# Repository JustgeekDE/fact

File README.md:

# Simple Fact
## Overview
Simple Fact (a simple **F**lash **a**nd **c**amera **t**rigger) is a smallish ([SoB 5x5](http://dangerousprototypes.com/docs/Sick_of_Beige_standard_PCB_sizes_v1.0)) tool to automatically trigger a a camera or camera flash based on sounds or light impulses.

The whole system is planned to be Arduino compatible to allow easy extension.

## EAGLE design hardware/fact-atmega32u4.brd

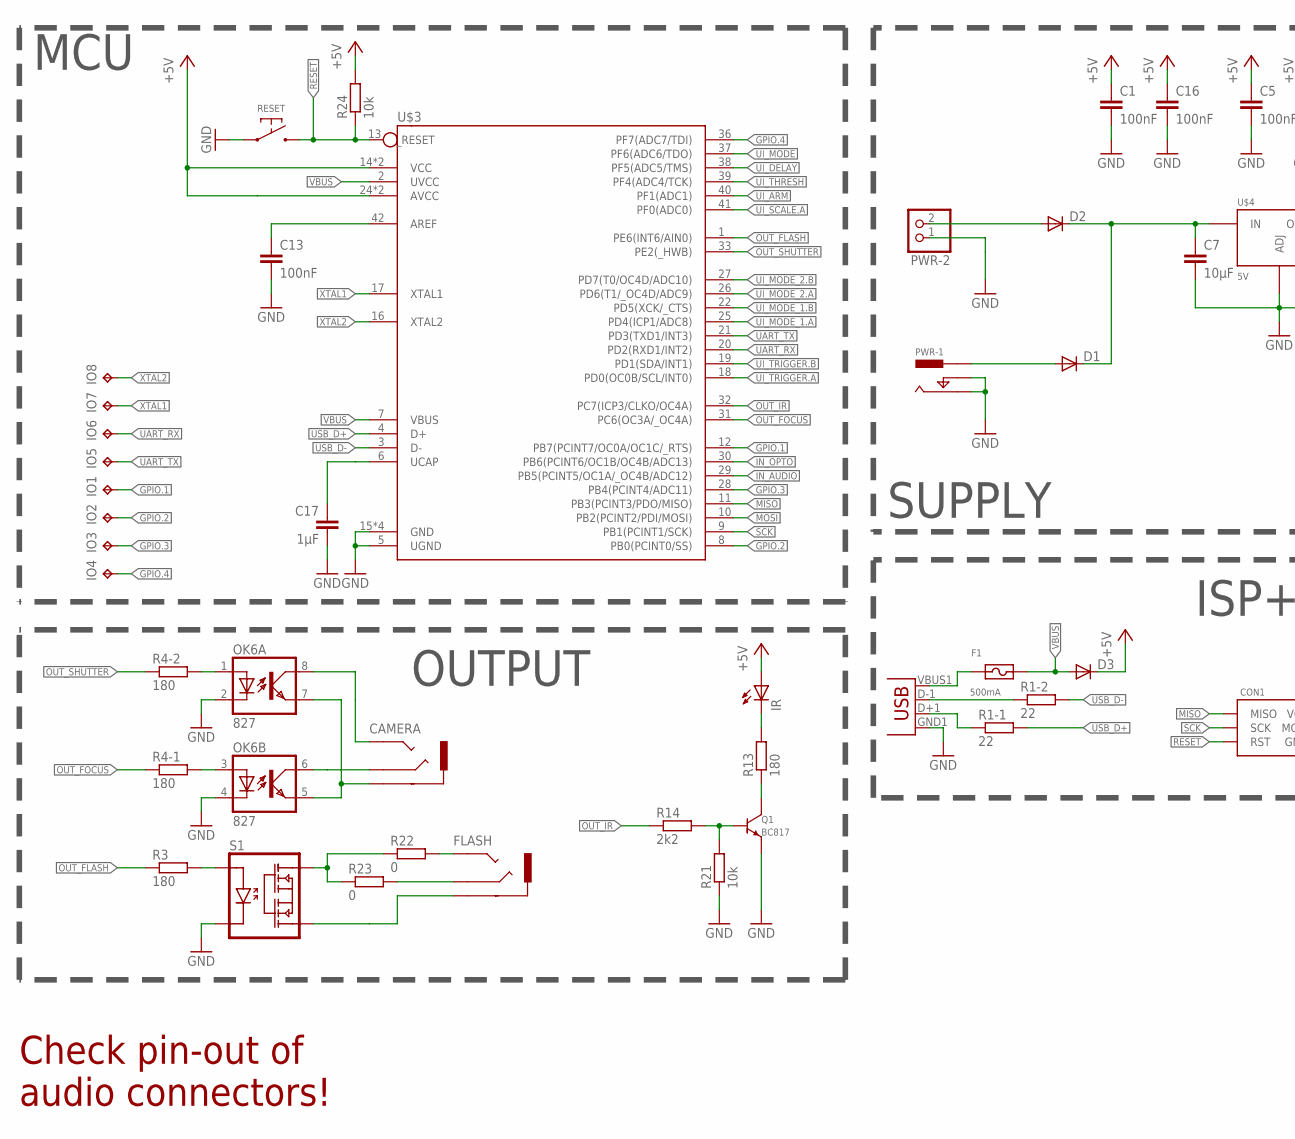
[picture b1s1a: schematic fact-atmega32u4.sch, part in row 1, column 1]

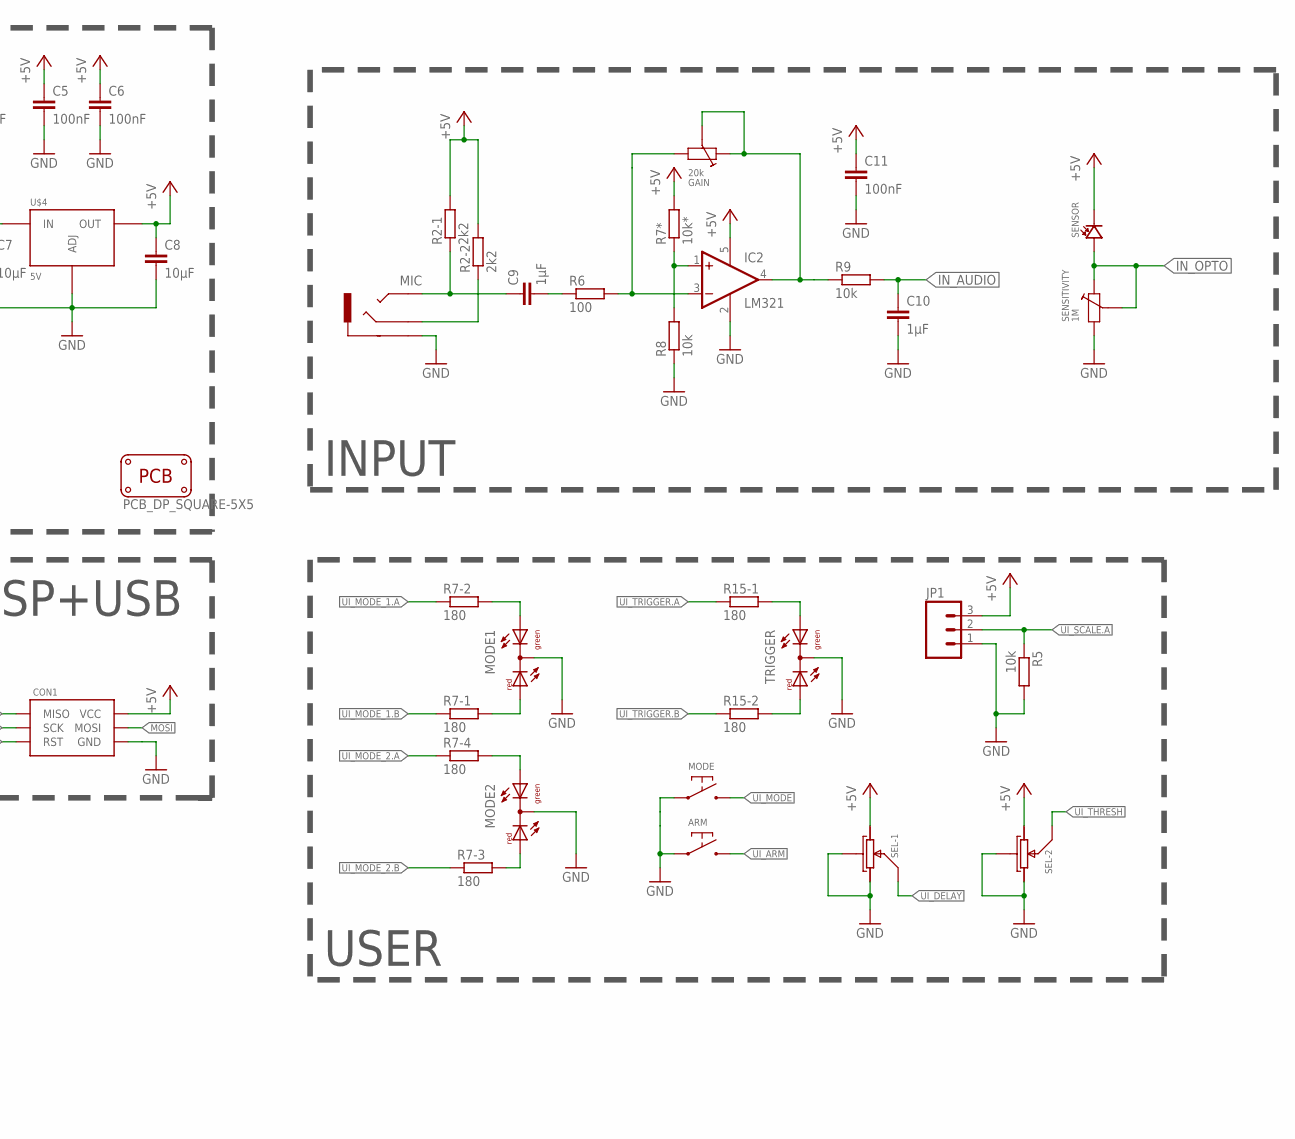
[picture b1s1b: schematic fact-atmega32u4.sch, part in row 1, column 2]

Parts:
ARM: SWITCH-DEFAULT_OFF-DEFAULT; SWITCH-GENERIC-4_PIN
C1, C5, C6, C11, C13, C16: 100nF; C0603
C7, C8: 10µF; C0603
C9, C10, C17: 1µF; C0603
CAMERA: AUDIO-STEREO2MM5; AUDIO-STEREO-2MM5-SJ1-2503A
CON1: ISP-6_PIN-POGO; POGO-1.27-6_PIN-MADWORM
D1, D2, D3: DIODESOD; SOD-323
F1: 500mA; SMD-0805
FLASH: AUDIO-STEREODEALEXTREME; AUDIO-STEREO-3MM5-ST-009
GAIN: 20k; TRIM-POT-CA6-VS5
IC2: LM321; SOT23-5
IO1, IO2, IO3, IO4, IO5, IO6, IO7, IO8: TPTP15R; TP15R
IR: LED5MM
JP1: M03LOCK; 1X03_LOCK
MIC: AUDIO-STEREODEALEXTREME; AUDIO-STEREO-3MM5-ST-009
MODE: SWITCH-DEFAULT_OFF-DEFAULT; SWITCH-GENERIC-4_PIN
MODE1, MODE2: DUOLED-RG-C; DUOLED-C-5MM
OK6: 827; SMD08
PCB1: PCB_DP_SQUARE-5X5; DP5050_V1
PWR-1: POWER-BARREL_JACKEBAY; POWER-BARREL-2MM1-EBAY
PWR-2: PINHD-1X2; 1X02
Q1: BC817; SOT23
R1: 22; R-ARRAY-2X-0603
R2: 2k2; R-ARRAY-2X-0603
R3, R13: 180; R0603
R4, R15: 180; R-ARRAY-2X-0603
R5, R8, R9, R21, R24: 10k; R0603
R6: 100; R0603
R7: 180; R-ARRAY-4X-CTS-0603
R7*: 10k*; R0603
R14: 2k2; R0603
R22, R23: 0; R1206
RESET: SWITCH-DEFAULT_OFF-SMD-2_PIN; SWITCH-SMD-2_PIN-DX
S1: RELAYLH1500; SMD-06
SEL: DUAL-POT; POT-DUAL-P090
SENSITIVITY: 1M; TRIM-POT-CA6-VS5
SENSOR: PHOTODIODE; LED-5MM
TRIGGER: DUOLED-RG-C; DUOLED-C-5MM
U$3: ATMEGA32U4-QFN-HAND; QFN-44-NOPAD-LONGLEADS
U$4: 5V; SOT223
U$5: USB; USB-AB-MICRO-SMD_V03

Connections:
+5V: C1.1, C5.1, C6.1, C8.1, C11.1, C16.1, CON1.P$2 (VCC), D3.1 (C), IC2.5 (V+), IR.A, JP1.3, R2.P$1.2 (2), R2.P$2.2 (2), R7*.2, R24.2, SEL.P1-3 (B), SEL.P2-1 (A), SENSOR.K (C), U$3.14 (VCC), U$3.24 (AVCC), U$3.34 (VCC), U$3.44 (AVCC), U$4.2 (OUT), U$4.4 (OUT)
GND: ARM.P$1, ARM.P$2, C1.2, C5.2, C6.2, C7.2, C8.2, C10.2, C11.2, C13.2, C16.2, C17.2, CON1.P$6 (GND), IC2.2 (V-), JP1.1, MIC.P$1.1 (SLEEVE), MIC.P$1.2 (SLEEVE), MODE.P$1, MODE.P$2, MODE1.C, MODE2.C, OK6.2 (C), OK6.4 (C), PWR-1.P$2 (SWITCH), PWR-1.P$3 (OUTER), PWR-2.1, Q1.P$2 (EMITTER), R5.2, R8.1, R21.1, RESET.P$1, S1.2 (LED-C), SEL.CENTER (SHIELD), SEL.G1-S (SHIELD), SEL.G2-S (SHIELD), SEL.P1-1 (A), SEL.P2-3 (B), SENSITIVITY.P$2, TRIGGER.C, U$3.5 (UGND), U$3.15 (GND), U$3.23 (GND), U$3.35 (GND), U$3.43 (GND), U$4.1 (ADJ), U$5.GND1 (GND)
GPIO.1: IO1.TP, U$3.12 (PB7(PCINT7/OC0A/OC1C/_RTS))
GPIO.2: IO2.TP, U$3.8 (PB0(PCINT0/SS))
GPIO.3: IO3.TP, U$3.28 (PB4(PCINT4/ADC11))
GPIO.4: IO4.TP, U$3.36 (PF7(ADC7/TDI))
HV_OUT: R22.1, R23.1, S1.6 (R1)
HV_RING: FLASH.P$2 (RING), R23.2
HV_SLEEVE: FLASH.P$1.1 (SLEEVE), FLASH.P$1.2 (SLEEVE), S1.4 (R2)
HV_TIP: FLASH.P$3.1 (TIP), FLASH.P$3.2 (TIP), R22.2
IN_AUDIO: C10.1, R9.2, U$3.29 (PB5(PCINT5/OC1A/_OC4B/ADC12))
IN_OPTO: SENSITIVITY.CENTER, SENSITIVITY.P$1, SENSOR.A, U$3.30 (PB6(PCINT6/OC1B/OC4B/ADC13))
MISO: CON1.P$1 (MISO), U$3.11 (PB3(PCINT3/PDO/MISO))
MOSI: CON1.P$4 (MOSI), U$3.10 (PB2(PCINT2/PDI/MOSI))
unnamed: C7.1, D1.1 (C), D2.1 (C), U$4.3 (IN)
unnamed: F1.1, U$5.VBUS1 (VBUS)
unnamed: R1.P$2.1 (1), U$5.D-1 (D-)
unnamed: D1.2 (A), PWR-1.P$4 (CENTER)
unnamed: R1.P$1.1 (1), U$5.D+1 (D+)
unnamed: D2.2 (A), PWR-2.2
unnamed: CAMERA.P$1 (SLEEVE), OK6.5 (EMIT), OK6.7 (EMIT)
unnamed: CAMERA.P$4 (RING), OK6.6 (COL)
unnamed: CAMERA.P$2 (TIP), CAMERA.P$3 (TIP), OK6.8 (COL)
unnamed: OK6.1 (A), R4.P$2.2 (2)
unnamed: MIC.P$2 (RING), R2.P$2.1 (1)
unnamed: C9.1, MIC.P$3.1 (TIP), MIC.P$3.2 (TIP), R2.P$1.1 (1)
unnamed: IC2.1 (+IN), R7*.1, R8.2
unnamed: C9.2, R6.1
unnamed: GAIN.P$2, IC2.3 (-IN), R6.2
unnamed: GAIN.CENTER, GAIN.P$1, IC2.4 (OUT), R9.1
unnamed: R3.2, S1.1 (LED-A)
unnamed: OK6.3 (A), R4.P$1.2 (2)
unnamed: Q1.P$3 (COLLECTOR), R13.1
unnamed: IR.K (C), R13.2
unnamed: Q1.P$1 (BASE), R14.2, R21.2
unnamed: MODE1.AX (AG), R7.P$2.2 (2)
unnamed: MODE1.AR, R7.P$1.2 (2)
unnamed: R15.P$1.2 (2), TRIGGER.AX (AG)
unnamed: R15.P$2.2 (2), TRIGGER.AR
unnamed: MODE2.AX (AG), R7.P$4.2 (2)
unnamed: MODE2.AR, R7.P$3.2 (2)
unnamed: C13.1, U$3.42 (AREF)
unnamed: C17.1, U$3.6 (UCAP)
OUT_FLASH: R3.1, U$3.1 (PE6(INT6/AIN0))
OUT_FOCUS: R4.P$1.1 (1), U$3.31 (PC6(OC3A/_OC4A))
OUT_IR: R14.1, U$3.32 (PC7(ICP3/CLKO/OC4A))
OUT_SHUTTER: R4.P$2.1 (1), U$3.33 (PE2(_HWB))
RESET: CON1.P$5 (RST), R24.1, RESET.P$2, U$3.13 (_RESET)
SCK: CON1.P$3 (SCK), U$3.9 (PB1(PCINT1/SCK))
UART_RX: IO6.TP, U$3.20 (PD2(RXD1/INT2))
UART_TX: IO5.TP, U$3.21 (PD3(TXD1/INT3))
UI_ARM: ARM.P$3, ARM.P$4, U$3.40 (PF1(ADC1))
UI_DELAY: SEL.P1-2 (M), U$3.38 (PF5(ADC5/TMS))
UI_MODE: MODE.P$3, MODE.P$4, U$3.37 (PF6(ADC6/TDO))
UI_MODE_1.A: R7.P$2.1 (1), U$3.25 (PD4(ICP1/ADC8))
UI_MODE_1.B: R7.P$1.1 (1), U$3.22 (PD5(XCK/_CTS))
UI_MODE_2.A: R7.P$4.1 (1), U$3.26 (PD6(T1/_OC4D/ADC9))
UI_MODE_2.B: R7.P$3.1 (1), U$3.27 (PD7(T0/OC4D/ADC10))
UI_SCALE.A: JP1.2, R5.1, U$3.41 (PF0(ADC0))
UI_THRESH: SEL.P2-2 (M), U$3.39 (PF4(ADC4/TCK))
UI_TRIGGER.A: R15.P$1.1 (1), U$3.18 (PD0(OC0B/SCL/INT0))
UI_TRIGGER.B: R15.P$2.1 (1), U$3.19 (PD1(SDA/INT1))
USB_D+: R1.P$1.2 (2), U$3.4 (D+)
USB_D-: R1.P$2.2 (2), U$3.3 (D-)
VBUS: D3.2 (A), F1.2, U$3.2 (UVCC), U$3.7 (VBUS)
XTAL1: IO7.TP, U$3.17 (XTAL1)
XTAL2: IO8.TP, U$3.16 (XTAL2)

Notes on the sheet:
INPUT
OUTPUT
USER
SUPPLY
MCU
Check pin-out of audio connectors!
ISP+USB

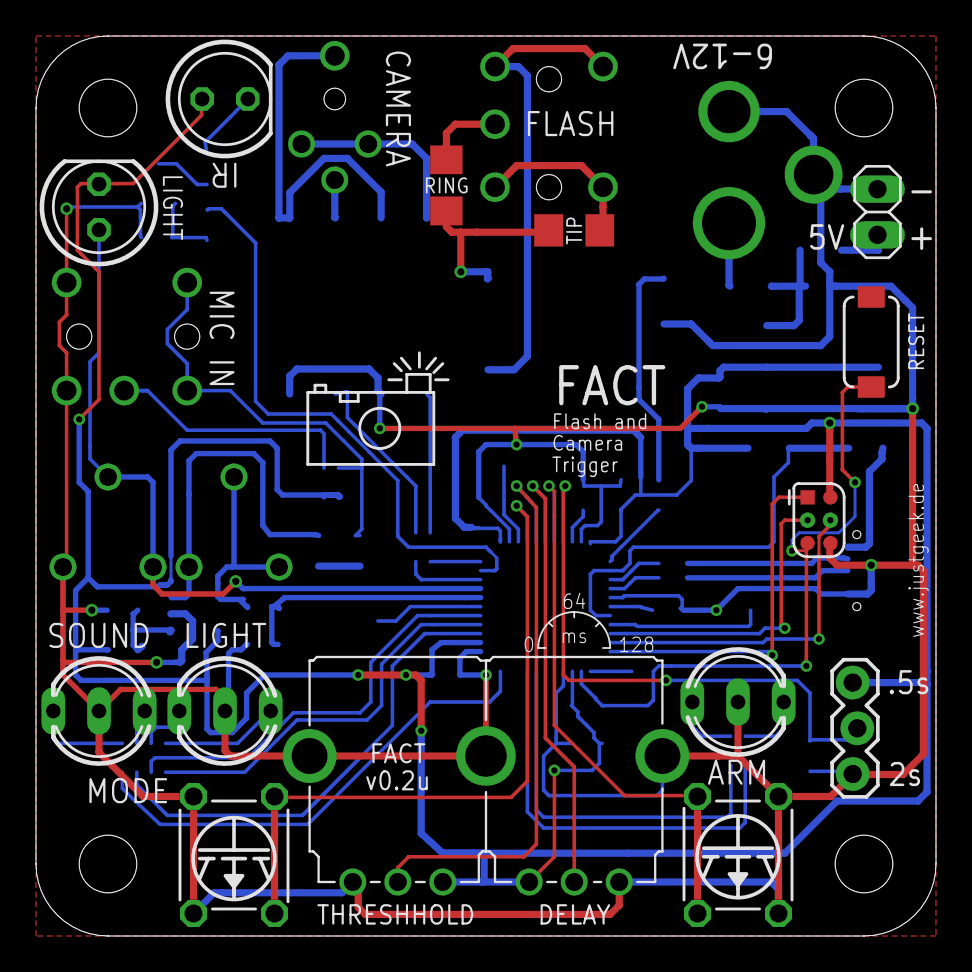
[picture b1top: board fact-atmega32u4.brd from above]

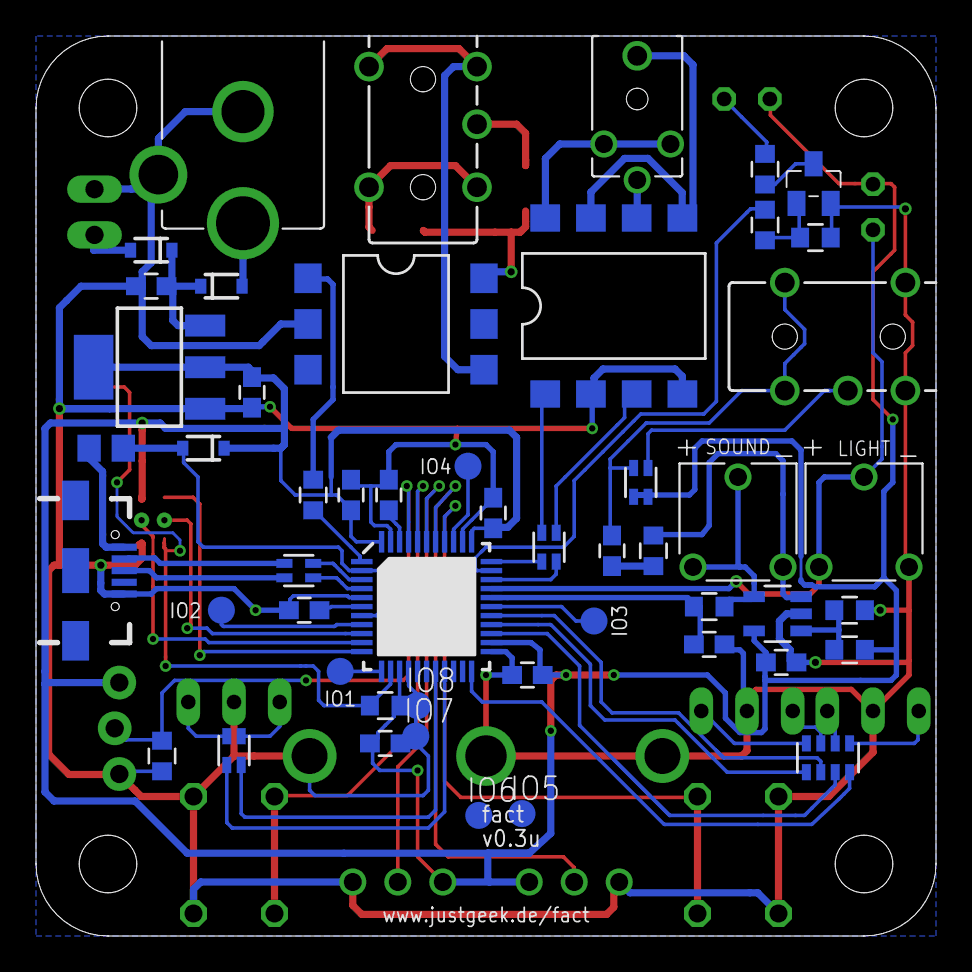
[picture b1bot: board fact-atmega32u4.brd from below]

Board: 2 copper layers, 50.0 x 50.0 mm, 70 parts (52 on the bottom side), 67 nets.

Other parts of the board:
U$1, U$2: LOGO-JUSTGEEK-XS
U$6, U$7: LOGO-JUSTGEEK-XXXS-MASK

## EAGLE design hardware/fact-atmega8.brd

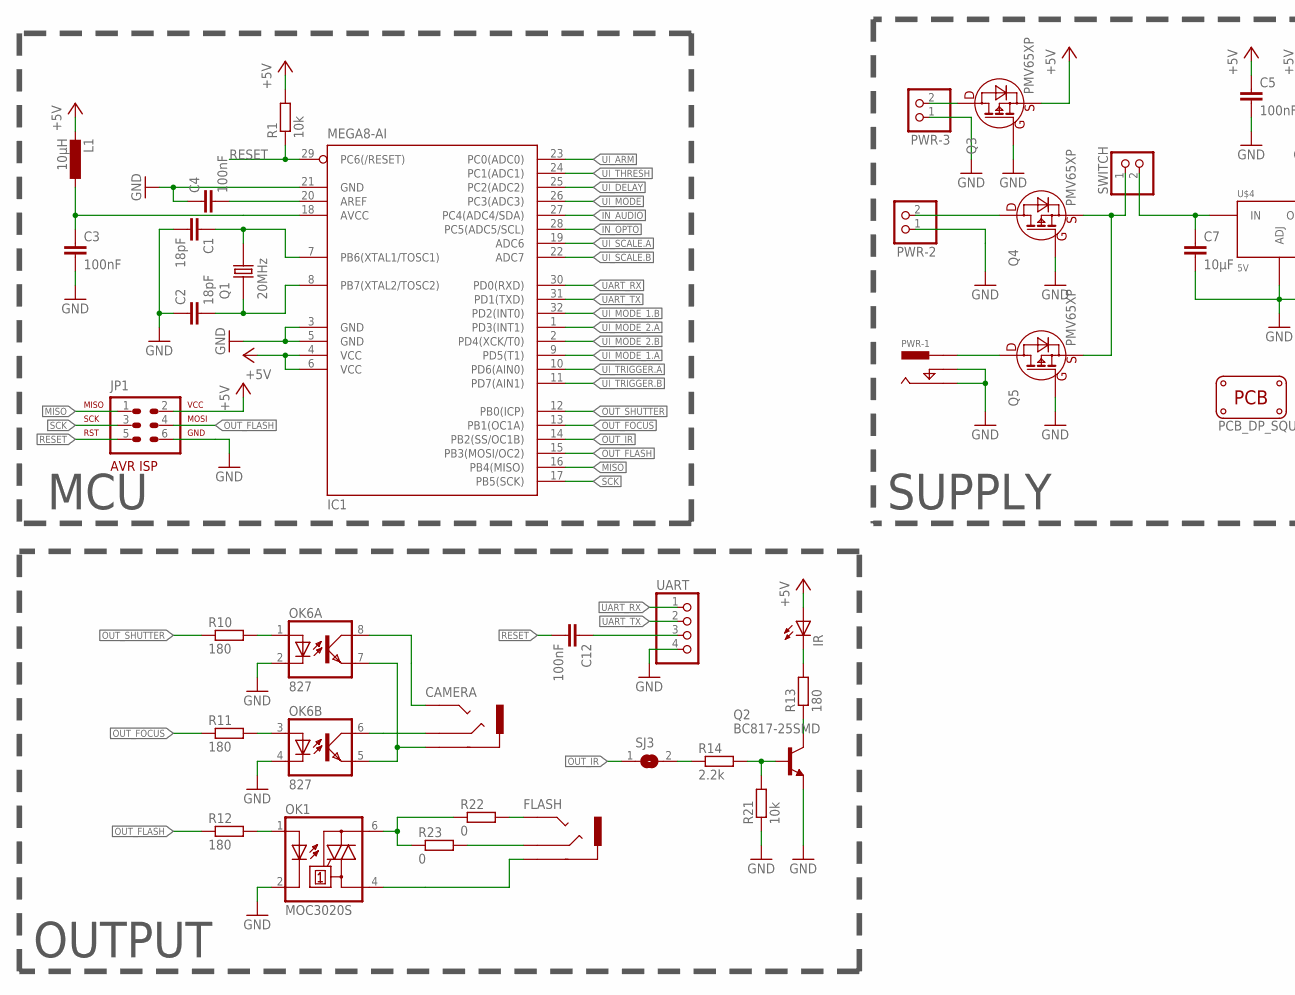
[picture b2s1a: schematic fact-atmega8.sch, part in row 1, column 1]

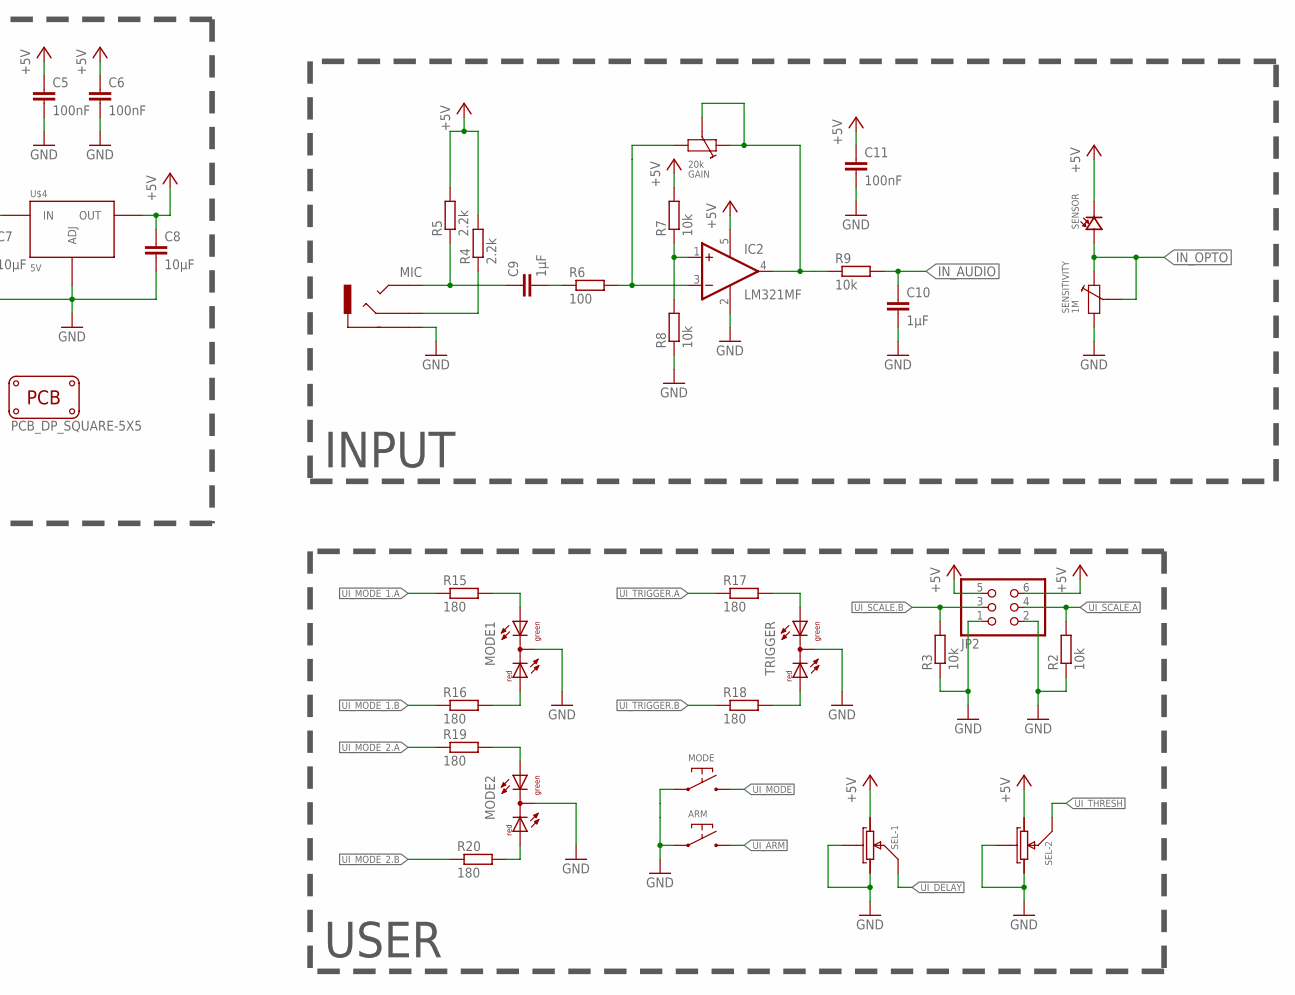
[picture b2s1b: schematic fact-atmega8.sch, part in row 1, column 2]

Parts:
ARM: SWITCH-DEFAULT_OFF; SWITCH-GENERIC-4_PIN
C1, C2: 18pF; C0603
C3, C4, C5, C6, C11, C12: 100nF; C0603
C7, C8: 10µF; C0603
C9, C10: 1µF; C0603
CAMERA: AUDIO-STEREO2MM5; AUDIO-STEREO-2MM5-SJ1-2503A
FLASH: AUDIO-STEREOCONRAD; AUDIO-STEREO-CONRAD-KB3-3_PIN
GAIN: 20k; TRIM-POT-CA6-VS5
IC1: MEGA8-AI; TQFP32-08
IC2: LM321MF; SOT23-5
IR: LED5MM
JP1: AVR-ISP-6VERT; AVR-ISP-6
JP2: PINHD-2X3; 2X03
L1: 10µH; R0805
MIC: AUDIO-STEREOCONRAD-KB3; AUDIO-STEREO-CONRAD-KB3-3_PIN
MODE: SWITCH-DEFAULT_OFF; SWITCH-GENERIC-4_PIN
MODE1, MODE2: DUOLED-RG-C; DUOLED-C-5MM
OK1: MOC3020S; DIL6-SMD
OK6: 827; SMD08
PCB1: PCB_DP_SQUARE-5X5; DP5050_V1
PWR-1: POWER-BARREL_JACKPJ-102A; POWER-BARREL-2MM1-PJ_102A
PWR-2, PWR-3: PINHD-1X2; 1X02
Q1: 20MHz; CRYSTAL-SMD-5MM_X_3.2MM
Q2: BC817-25SMD; SOT23-BEC
Q3, Q4, Q5: PMV65XP; SOT23
R1, R2, R3, R7, R8, R9, R21: 10k; R0603
R4, R5, R14: 2.2k; R0603
R6: 100; R0603
R10, R11, R12, R13, R15, R16, R17, R18, R19, R20: 180; R0603
R22, R23: 0; R1206
SEL: DUAL-POT; POT-DUAL-P090
SENSITIVITY: 1M; TRIM-POT-CA6-VS5
SENSOR: PHOTODIODE; LED-5MM
SJ3: SJ
SWITCH: PINHD-1X2; 1X02
TRIGGER: DUOLED-RG-C; DUOLED-C-5MM
U$4: 5V; SOT223
UART: PINHD-1X4; 1X04

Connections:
+5V: C5.1, C6.1, C8.1, C11.1, IC1.4 (VCC), IC1.6 (VCC), IC2.5 (V+), IR.A, JP1.2, JP2.5, JP2.6, L1.2, Q3.P$2 (SOURCE), R1.2, R4.2, R5.2, R7.2, SEL.P1-3 (B), SEL.P2-1 (A), SENSOR.K (C), U$4.2 (OUT)
GND: ARM.P$1, ARM.P$2, C1.2, C2.1, C3.2, C4.1, C5.2, C6.2, C7.2, C8.2, C10.2, C11.2, IC1.3 (GND), IC1.5 (GND), IC1.21 (GND), IC2.2 (V-), JP1.6, JP2.1, JP2.2, MIC.2.1 (SLEEVE), MIC.2.2 (SLEEVE), MODE.P$1, MODE.P$2, MODE1.C, MODE2.C, OK1.2 (C), OK6.2 (C), OK6.4 (C), PWR-1.P$2 (OUTER), PWR-1.P$3 (SWITCH), PWR-2.1, PWR-3.1, Q2.E, Q3.P$1 (GATE), Q4.P$1 (GATE), Q5.P$1 (GATE), R2.1, R3.1, R8.1, R21.1, SEL.CENTER (SHIELD), SEL.G1-S (SHIELD), SEL.G2-S (SHIELD), SEL.P1-1 (A), SEL.P2-3 (B), SENSITIVITY.P$2, TRIGGER.C, U$4.1 (ADJ), U$4.4 (ADJ), UART.4
HV_OUT: OK1.6 (A2), R22.1, R23.1
HV_RING: FLASH.2.1 (RING), FLASH.2.2 (RING), R23.2
HV_SLEEVE: FLASH.1 (SLEEVE), OK1.4 (A1)
HV_TIP: FLASH.3 (TIP), R22.2
IN_AUDIO: C10.1, IC1.27 (PC4(ADC4/SDA)), R9.2
IN_OPTO: IC1.28 (PC5(ADC5/SCL)), SENSITIVITY.CENTER, SENSITIVITY.P$1, SENSOR.A
MISO: IC1.16 (PB4(MISO)), JP1.1
unnamed: R14.1, SJ3.2
unnamed: C7.1, SWITCH.2, U$4.3 (IN)
unnamed: C3.1, IC1.18 (AVCC), L1.1
unnamed: C4.2, IC1.20 (AREF)
unnamed: PWR-1.P$1 (CENTER), Q5.P$3 (DRAIN)
unnamed: C1.1, IC1.7 (PB6(XTAL1/TOSC1)), Q1.P$2 (C2)
unnamed: C2.2, IC1.8 (PB7(XTAL2/TOSC2)), Q1.P$1 (C1)
unnamed: PWR-2.2, Q4.P$3 (DRAIN)
unnamed: Q4.P$2 (SOURCE), Q5.P$2 (SOURCE), SWITCH.1
unnamed: PWR-3.2, Q3.P$3 (DRAIN)
unnamed: CAMERA.P$1 (SLEEVE), OK6.5 (EMIT), OK6.7 (EMIT)
unnamed: CAMERA.P$4 (RING), OK6.6 (COL)
unnamed: CAMERA.P$2 (TIP), CAMERA.P$3 (TIP), OK6.8 (COL)
unnamed: OK6.1 (A), R10.2
unnamed: MIC.1 (RING), R4.1
unnamed: C9.1, MIC.3 (TIP), R5.1
unnamed: IC2.1 (+IN), R7.1, R8.2
unnamed: C9.2, R6.1
unnamed: GAIN.P$2, IC2.3 (-IN), R6.2
unnamed: GAIN.CENTER, GAIN.P$1, IC2.4 (OUT), R9.1
unnamed: OK1.1 (A), R12.2
unnamed: OK6.3 (A), R11.2
unnamed: Q2.C, R13.1
unnamed: IR.K (C), R13.2
unnamed: Q2.B, R14.2, R21.2
unnamed: MODE1.AX (AG), R15.2
unnamed: MODE1.AR, R16.2
unnamed: R17.2, TRIGGER.AX (AG)
unnamed: R18.2, TRIGGER.AR
unnamed: C12.1, UART.3
unnamed: MODE2.AX (AG), R19.2
unnamed: MODE2.AR, R20.2
OUT_FLASH: IC1.15 (PB3(MOSI/OC2)), JP1.4, R12.1
OUT_FOCUS: IC1.13 (PB1(OC1A)), R11.1
OUT_IR: IC1.14 (PB2(SS/OC1B)), SJ3.1
OUT_SHUTTER: IC1.12 (PB0(ICP)), R10.1
RESET: C12.2, IC1.29 (PC6(/RESET)), JP1.5, R1.1
SCK: IC1.17 (PB5(SCK)), JP1.3
UART_RX: IC1.30 (PD0(RXD)), UART.1
UART_TX: IC1.31 (PD1(TXD)), UART.2
UI_ARM: ARM.P$3, ARM.P$4, IC1.23 (PC0(ADC0))
UI_DELAY: IC1.25 (PC2(ADC2)), SEL.P1-2 (M)
UI_MODE: IC1.26 (PC3(ADC3)), MODE.P$3, MODE.P$4
UI_MODE_1.A: IC1.9 (PD5(T1)), R15.1
UI_MODE_1.B: IC1.32 (PD2(INT0)), R16.1
UI_MODE_2.A: IC1.1 (PD3(INT1)), R19.1
UI_MODE_2.B: IC1.2 (PD4(XCK/T0)), R20.1
UI_SCALE.A: IC1.19 (ADC6), JP2.4, R2.2
UI_SCALE.B: IC1.22 (ADC7), JP2.3, R3.2
UI_THRESH: IC1.24 (PC1(ADC1)), SEL.P2-2 (M)
UI_TRIGGER.A: IC1.10 (PD6(AIN0)), R17.1
UI_TRIGGER.B: IC1.11 (PD7(AIN1)), R18.1

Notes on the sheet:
INPUT
OUTPUT
USER
SUPPLY
MCU

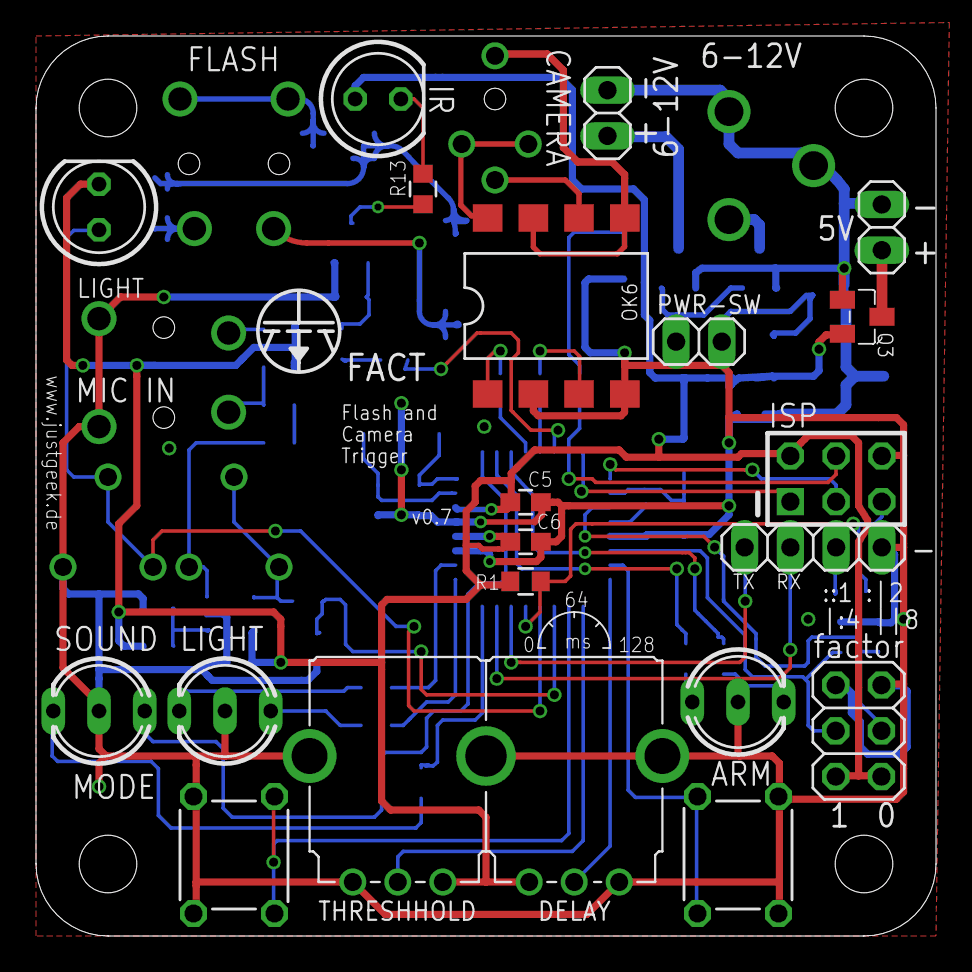
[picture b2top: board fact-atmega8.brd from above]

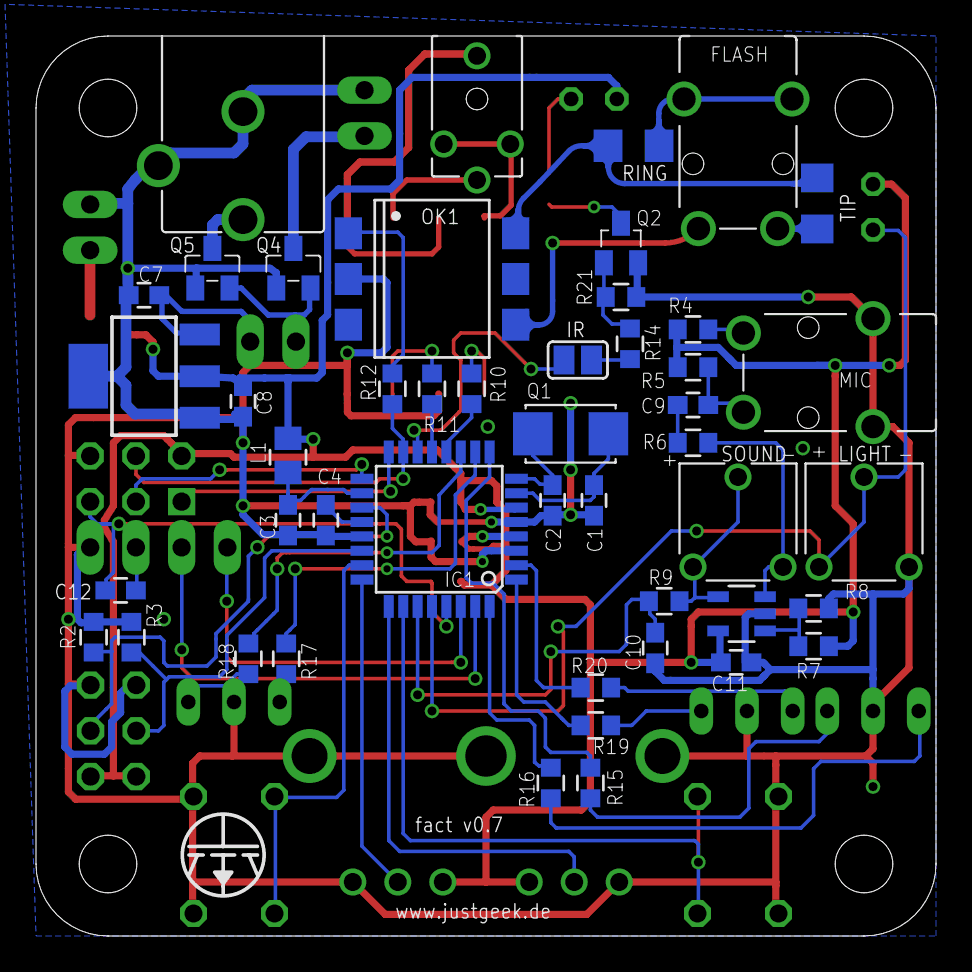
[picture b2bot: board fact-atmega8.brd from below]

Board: 2 copper layers, 50.0 x 50.0 mm, 70 parts (48 on the bottom side), 61 nets.

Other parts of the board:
U$1, U$2: LOGO-JUSTGEEK-XS

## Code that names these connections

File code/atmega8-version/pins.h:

#ifndef __PINS_H
#define __PINS_H


#define SET_BIT(port,bit)   (port |=  (1 << bit))
#define CLEAR_BIT(port,bit) (port &= ~(1 << bit))
#define READ_BIT(port,bit)  ((port & (1 << bit)) ? 1 : 0)



/* User interface Buttons */
#define UI_BUTTON_PORT PORTC
#define UI_BUTTON_DDR  DDRC
#define UI_BUTTON_PIN  PINC

#define UI_BUTTON_ARM_PORT PORTC
#define UI_BUTTON_ARM_DDR  DDRC
#define UI_BUTTON_ARM_PIN  PINC
#define UI_BUTTON_ARM_BIT  PC0

#define UI_BUTTON_MODE_PORT PORTC
#define UI_BUTTON_MODE_DDR  DDRC
#define UI_BUTTON_MODE_PIN  PINC
#define UI_BUTTON_MODE_BIT  PC3

/* User interface Knobs */
#define UI_POT_THRESH_PORT PORTC
#define UI_POT_THRESH_DDR  DDRC
#define UI_POT_THRESH_PIN  PINC
#define UI_POT_THRESH_BIT  PC1
#define UI_POT_THRESH_CHANNEL 2

#define UI_POT_DELAY_PORT PORTC
#define UI_POT_DELAY_DDR  DDRC
#define UI_POT_DELAY_PIN  PINC
#define UI_POT_DELAY_BIT  PC2
#define UI_POT_DELAY_CHANNEL 1

/* User interface Jumper */
#define UI_JUMPER_A_CHANNEL 6
#define UI_JUMPER_B_CHANNEL 7

/* User Interface LEDs */
#define UI_LED_PORT PORTD
#define UI_LED_DDR  DDRD
#define UI_LED_PIN  PIND

#define UI_LED_SOUND_GREEN_PORT PORTD
#define UI_LED_SOUND_GREEN_DDR  DDRD
#define UI_LED_SOUND_GREEN_PIN  PIND
#define UI_LED_SOUND_GREEN_BIT  PD2

#define UI_LED_SOUND_RED_PORT PORTD
#define UI_LED_SOUND_RED_DDR  DDRD
#define UI_LED_SOUND_RED_PIN  PIND
#define UI_LED_SOUND_RED_BIT  PD5

#define UI_LED_LIGHT_GREEN_PORT PORTD
#define UI_LED_LIGHT_GREEN_DDR  DDRD
#define UI_LED_LIGHT_GREEN_PIN  PIND
#define UI_LED_LIGHT_GREEN_BIT  PD4

#define UI_LED_LIGHT_RED_PORT PORTD
#define UI_LED_LIGHT_RED_DDR  DDRD
#define UI_LED_LIGHT_RED_PIN  PIND
#define UI_LED_LIGHT_RED_BIT  PD3

#define UI_LED_ARMED_GREEN_PORT PORTD
#define UI_LED_ARMED_GREEN_DDR  DDRD
#define UI_LED_ARMED_GREEN_PIN  PIND
#define UI_LED_ARMED_GREEN_BIT  PD6

#define UI_LED_ARMED_RED_PORT PORTD
#define UI_LED_ARMED_RED_DDR  DDRD
#define UI_LED_ARMED_RED_PIN  PIND
#define UI_LED_ARMED_RED_BIT  PD7

#define UI_LED_MODE_BITMASK ((1 << UI_LED_SOUND_GREEN_BIT) | (1 << UI_LED_SOUND_RED_BIT) | (1 << UI_LED_LIGHT_GREEN_BIT) | (1 << UI_LED_LIGHT_RED_BIT))
#define UI_LED_BITMASK (UI_LED_MODE_BITMASK | (1 << UI_LED_ARMED_GREEN_BIT) | (1 << UI_LED_ARMED_RED_BIT))

/* Data input */
#define SENSOR_SOUND_PORT    PORTC
#define SENSOR_SOUND_DDR     DDRC
#define SENSOR_SOUND_PIN     PINC
#define SENSOR_SOUND_BIT     PC4
#define SENSOR_SOUND_CHANNEL 4

#define SENSOR_LIGHT_PORT    PORTC
#define SENSOR_LIGHT_DDR     DDRC
#define SENSOR_LIGHT_PIN     PINC
#define SENSOR_LIGHT_BIT     PC5
#define SENSOR_LIGHT_CHANNEL 5

/* Trigger outputs */
#define TRIGGER_PORT PORTB
#define TRIGGER_DDR  DDRB
#define TRIGGER_PIN  PINB

#define TRIGGER_SHUTTER_PORT PORTB
#define TRIGGER_SHUTTER_DDR  DDRB
#define TRIGGER_SHUTTER_PIN  PINB
#define TRIGGER_SHUTTER_BIT  PB0

#define TRIGGER_FOCUS_PORT PORTB
#define TRIGGER_FOCUS_DDR  DDRB
#define TRIGGER_FOCUS_PIN  PINB
#define TRIGGER_FOCUS_BIT  PB1

#define TRIGGER_FLASH_PORT PORTB
#define TRIGGER_FLASH_DDR  DDRB
#define TRIGGER_FLASH_PIN  PINB
#define TRIGGER_FLASH_BIT  PB3

#define TRIGGER_IR_PORT PORTB
#define TRIGGER_IR_DDR  DDRB
#define TRIGGER_IR_PIN  PINB
#define TRIGGER_IR_BIT  PB2


#endif

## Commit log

2015-04-02 initial checkin

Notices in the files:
parts and their libraries:
SparkFun-Connectors: Licensing: Creative Commons ShareAlike 4.0 International - https://creativecommons.org/licenses/by-sa/4.0
